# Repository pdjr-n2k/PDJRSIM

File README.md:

# PDJRSIM - NMEA 2000 switch input module

This project provides a
[hardware design](./hardware/)
and associated
[firmware](./firmware)
for a 16-channel NMEA 2000 switch input module.

There is also a
[User Manual](./docs)
for a device constructed from these components.

**PDJRSIM** is a specialisation of
[NOP100](https://github.com/preeve9534/NOP100).

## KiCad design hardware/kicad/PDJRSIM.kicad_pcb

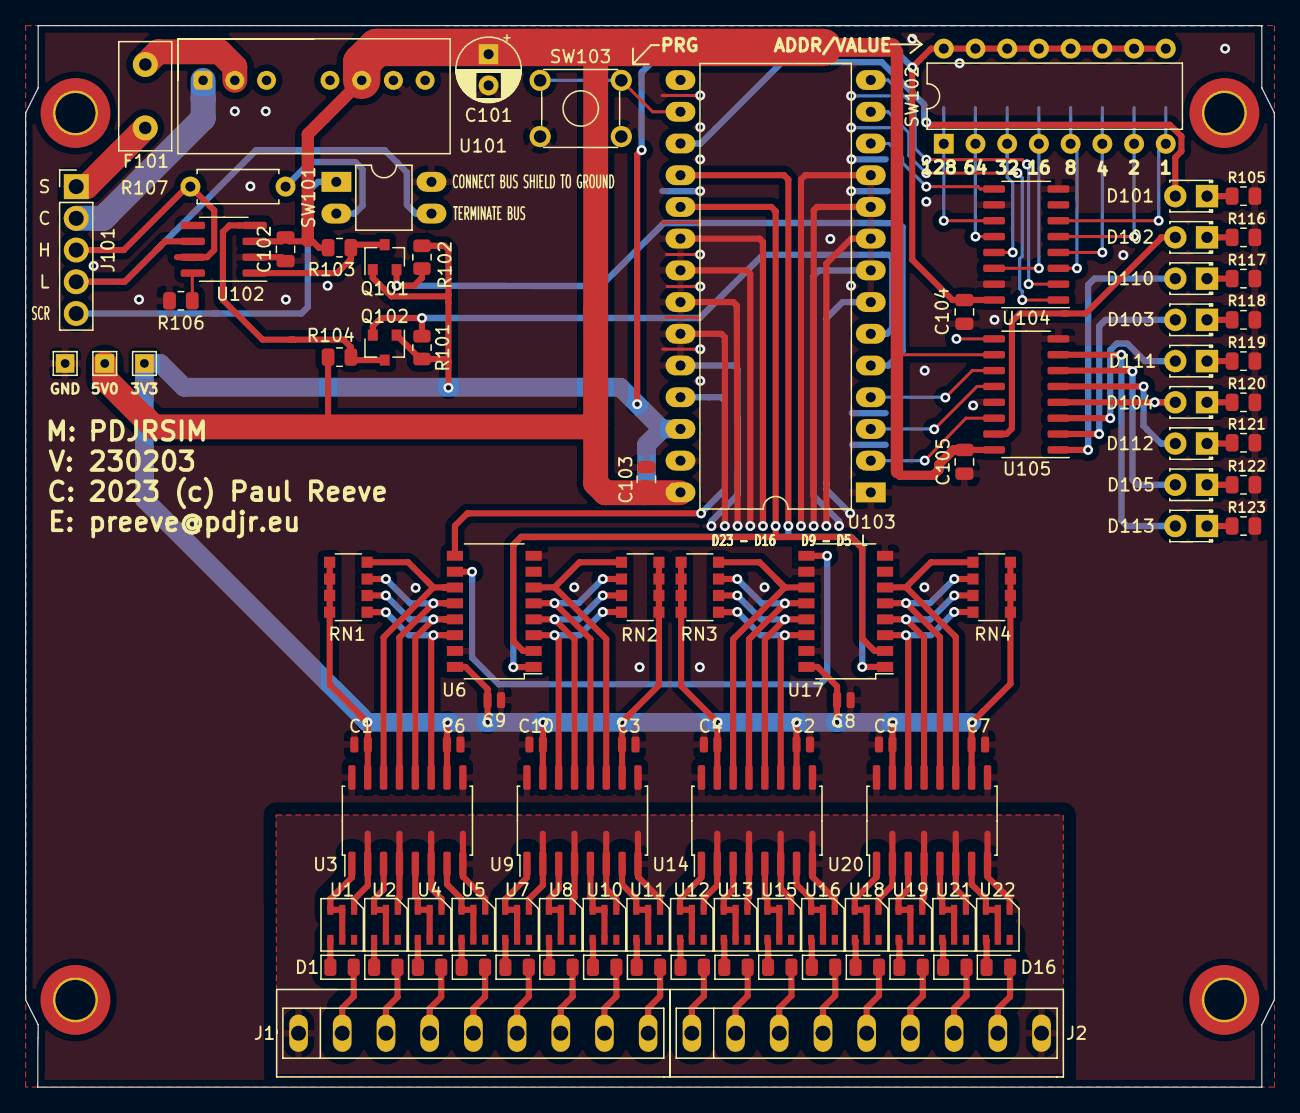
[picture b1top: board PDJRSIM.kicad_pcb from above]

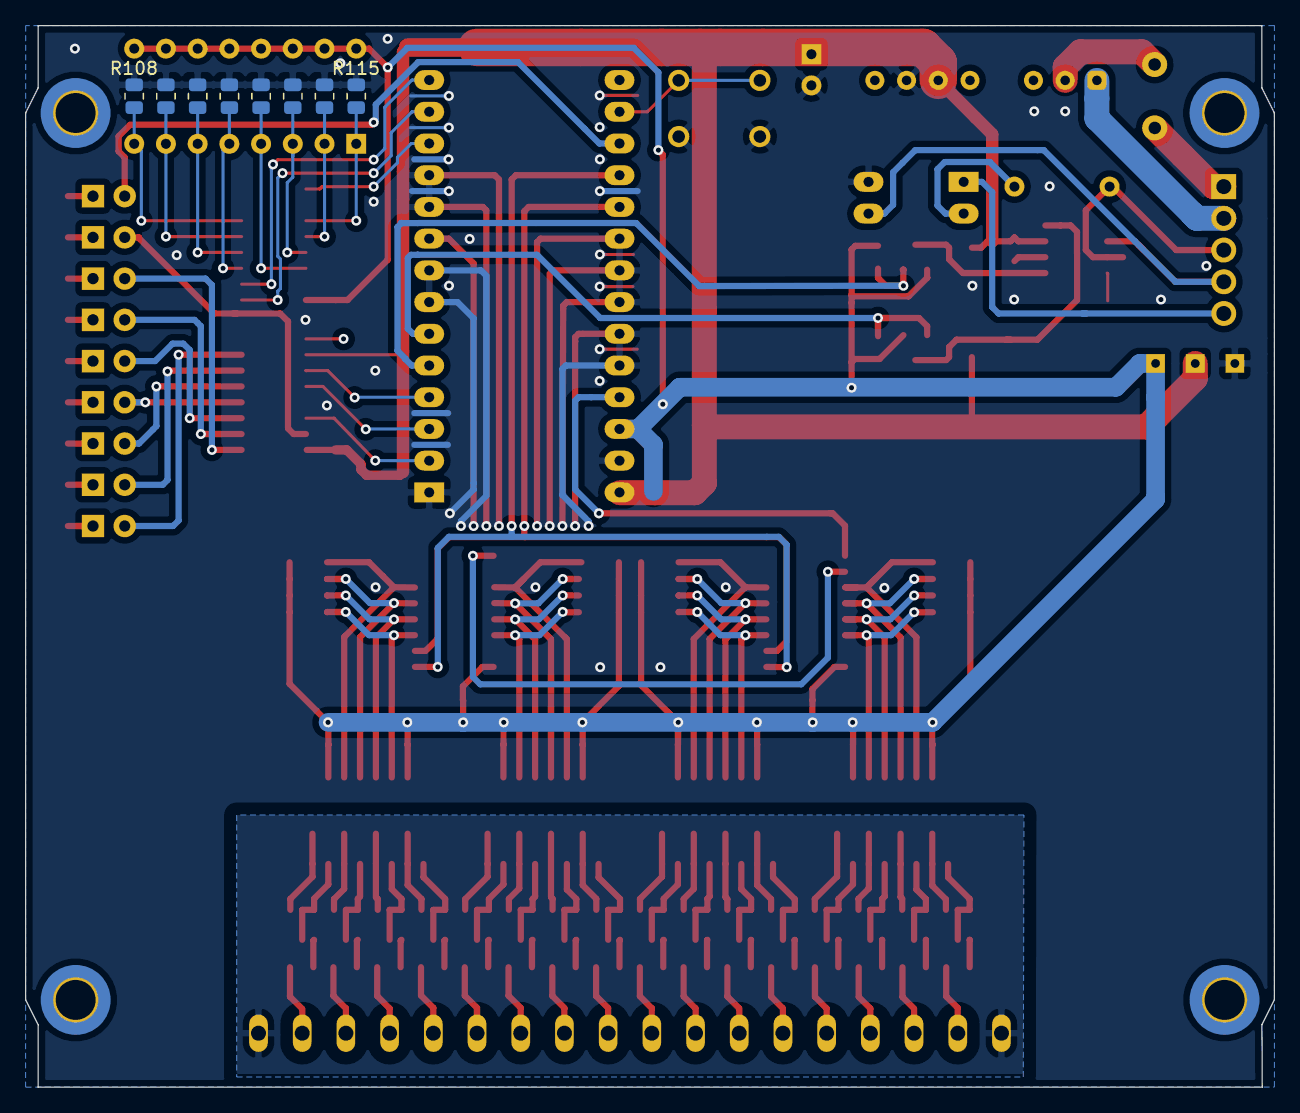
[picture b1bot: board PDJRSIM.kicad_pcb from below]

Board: 2 copper layers, 100.0 x 85.0 mm, 105 parts (8 on the bottom side), 117 nets.

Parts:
C1, C2, C3, C4, C5, C6, C7, C8, C9, C10: 100nF; C_0504_1310Metric
C101: 100nF; CP_Radial_D5.0mm_P2.50mm
C102, C103, C104, C105: 100nF; C_0805_2012Metric
D1, D2, D3, D4, D5, D6, D7, D8, D9, D10, D11, D12, D13, D14, D15, D16: D_Small; D_0805_2012Metric
D101, D102, D103, D104, D105, D110, D111, D112, D113: LED; LED_D1.8mm_W3.3mm_H2.4mm
F101: 1A; Fuse_Littelfuse_395Series
J1, J2: Screw_Terminal_01x09; 897-1357-9-PIN-3-5-CONN
J101: CAN; PinHeader_1x05_P2.54mm_Vertical
Q101, Q102: BSS138; SOT-23
R101, R102, R103, R104: 10K 0.125W; R_0805_2012Metric
R105, R116, R117, R118, R119, R120, R121, R122, R123: 560R; R_0805_2012Metric
R106, R108, R109, R110, R111, R112, R113, R114, R115: 4K7 0.125W; R_0805_2012Metric
R107: 120R 0.5W; R_Axial_DIN0207_L6.3mm_D2.5mm_P7.62mm_Horizontal
RN1, RN2, RN3, RN4: 4K; R_Array_Convex_4x1206
SW101: BUS; DIP-4_W7.62mm_LongPads
SW102: ADDR/VALUE; DIP-16_W7.62mm
SW103: PRG; SW_TH_Tactile_Omron_B3F-10xx
TEST 5V0, TEST 5V0#2: TestPoint_THTPad_1.5x1.5mm_Drill0.7mm
U1, U2, U4, U5, U7, U8, U10, U11, U12, U13, U15, U16, U18, U19, U21, U22: BCR401
U3, U9, U14, U20: ASCL-6400; SO-16_5.3x10.2mm_P1.27mm
U6, U17: 74LS165; SOP-16_4.4x10.4mm_P1.27mm
U101: TMR-2-2411; TMR_2411
U102: MCP2551-I-P; SOIC-8_3.9x4.9mm_P1.27mm
U103: Teensy_4.0; DIP-28_W15.24mm_LongPads
U104: 74HC165; SO-16_3.9x9.9mm_P1.27mm
U105: 74HCT595; SO-16_3.9x9.9mm_P1.27mm

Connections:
+3V3: C1.1, C2.1, C3.1, C4.1, C5.1, C6.1, C7.1, C8.1, C9.1, C10.1, C104.1, Q101.1, Q102.1, R101.2, R102.2, RN1.5, RN1.6, RN1.7, RN1.8, RN2.5, RN2.6, RN2.7, RN2.8, RN3.5, RN3.6, RN3.7, RN3.8, RN4.5, RN4.6, RN4.7, RN4.8, SW102.9, SW102.10, SW102.11, SW102.12, SW102.13, SW102.14, SW102.15, SW102.16, TEST 5V0.1, U3.10, U3.15, U6.16, U9.10, U9.15, U14.10, U14.15, U17.16, U20.10, U20.15, U103.26, U104.16
+5V: C101.1, C102.1, C103.1, C105.1, R103.2, R104.2, TEST 5V0#2.1, U101.6, U102.3, U103.28, U105.10, U105.16
/CAN_RX: Q102.2, R101.1, U103.6
/CAN_TX: Q101.2, R102.1, U103.5
/D16: U6.1, U17.1, U103.18
/D17: U6.2, U17.2, U103.19
/D23: U6.9, U103.25
/PISO_CP: U103.14, U104.2
/PISO_PL: U103.13, U104.1
/PISO_Q7: U103.12, U104.9
/PRG: SW103.1, SW103.2, U103.16
/SIPO_CLOCK: U103.4, U105.11
/SIPO_DATA: U103.2, U105.14
/SIPO_LATCH: U103.3, U105.12
GND: C1.2, C2.2, C3.2, C4.2, C5.2, C6.2, C7.2, C8.2, C9.2, C10.2, C101.2, C102.2, C103.2, C104.2, C105.2, R105.2, R106.1, R108.2, R109.2, R110.2, R111.2, R112.2, R113.2, R114.2, R115.2, R116.2, R117.2, R118.2, R119.2, R120.2, R121.2, R122.2, R123.2, SW101.4, SW103.3, SW103.4, U3.9, U3.16, U6.8, U6.15, U9.9, U9.16, U14.9, U14.16, U17.8, U17.10, U17.15, U20.9, U20.16, U101.7, U102.2, U103.1, U103.7, U103.8, U103.9, U103.10, U103.11, U103.20, U103.21, U103.22, U103.23, U103.24, U103.27, U104.8, U104.10, U104.15, U105.8, U105.13
unnamed: D1.1, U1.4
unnamed: D1.2, J1.2
unnamed: D2.1, U2.4
unnamed: D2.2, J1.3
unnamed: D3.1, U4.4
unnamed: D3.2, J1.4
unnamed: D4.1, U5.4
unnamed: D4.2, J1.5
unnamed: D5.1, U7.4
unnamed: D5.2, J1.6
unnamed: D6.1, U8.4
unnamed: D6.2, J1.7
unnamed: D7.1, U10.4
unnamed: D7.2, J1.8
unnamed: D8.1, U11.4
unnamed: D8.2, J1.9
unnamed: D9.1, U12.4
unnamed: D9.2, J2.1
unnamed: D10.1, U13.4
unnamed: D10.2, J2.2
unnamed: D11.1, U15.4
unnamed: D11.2, J2.3
unnamed: D12.1, U16.4
unnamed: D12.2, J2.4
unnamed: D13.1, U18.4
unnamed: D13.2, J2.5
unnamed: D14.1, U19.4
unnamed: D14.2, J2.6
unnamed: D15.1, U21.4
unnamed: D15.2, J2.7
unnamed: D16.1, U22.4
unnamed: D16.2, J2.8
unnamed: D101.1, R105.1
unnamed: D101.2, U103.17
unnamed: D102.1, R116.1
unnamed: D102.2, U105.15
unnamed: D103.1, R118.1
unnamed: D103.2, U105.2
unnamed: D104.1, R120.1
unnamed: D104.2, U105.4
unnamed: D105.1, R122.1
unnamed: D105.2, U105.6
unnamed: D110.1, R117.1
unnamed: D110.2, U105.1
unnamed: D111.1, R119.1
unnamed: D111.2, U105.3
unnamed: D112.1, R121.1
unnamed: D112.2, U105.5
unnamed: D113.1, R123.1
unnamed: D113.2, U105.7
unnamed: F101.1, J101.1
unnamed: F101.2, U101.2
unnamed: J1.1, J2.9, U1.1, U2.1, U3.2, U3.4, U3.6, U3.8, U4.1, U5.1, U7.1, U8.1, U9.2, U9.4, U9.6, U9.8, U10.1, U11.1, U12.1, U13.1, U14.2, U14.4, U14.6, U14.8, U15.1, U16.1, U18.1, U19.1, U20.2, U20.4, U20.6, U20.8, U21.1, U22.1
unnamed: J101.2, U101.1
unnamed: J101.3, R107.1, U102.7
unnamed: J101.4, SW101.3, U102.6
unnamed: J101.5, SW101.1
unnamed: Q101.3, R103.1, U102.1
unnamed: Q102.3, R104.1, U102.4
unnamed: R106.2, U102.8
unnamed: R107.2, SW101.2
unnamed: R108.1, SW102.8, U104.6
unnamed: R109.1, SW102.7, U104.5
unnamed: R110.1, SW102.6, U104.4
unnamed: R111.1, SW102.5, U104.3
unnamed: R112.1, SW102.4, U104.14
unnamed: R113.1, SW102.3, U104.13
unnamed: R114.1, SW102.2, U104.12
unnamed: R115.1, SW102.1, U104.11
unnamed: RN1.1, U3.11, U6.14
unnamed: RN1.2, U3.12, U6.13
unnamed: RN1.3, U3.13, U6.12
unnamed: RN1.4, U3.14, U6.11
unnamed: RN2.1, U6.6, U9.11
unnamed: RN2.2, U6.5, U9.12
unnamed: RN2.3, U6.4, U9.13
unnamed: RN2.4, U6.3, U9.14
unnamed: RN3.1, U14.11, U17.14
unnamed: RN3.2, U14.12, U17.13
unnamed: RN3.3, U14.13, U17.12
unnamed: RN3.4, U14.14, U17.11
unnamed: RN4.1, U17.6, U20.11
unnamed: RN4.2, U17.5, U20.12
unnamed: RN4.3, U17.4, U20.13
unnamed: RN4.4, U17.3, U20.14
unnamed: U1.2, U1.3, U1.5, U3.1
unnamed: U2.2, U2.3, U2.5, U3.3
unnamed: U3.5, U4.2, U4.3, U4.5
unnamed: U3.7, U5.2, U5.3, U5.5
unnamed: U7.2, U7.3, U7.5, U9.1
unnamed: U8.2, U8.3, U8.5, U9.3
unnamed: U9.5, U10.2, U10.3, U10.5
unnamed: U9.7, U11.2, U11.3, U11.5
unnamed: U12.2, U12.3, U12.5, U14.1
unnamed: U13.2, U13.3, U13.5, U14.3
unnamed: U14.5, U15.2, U15.3, U15.5
unnamed: U14.7, U16.2, U16.3, U16.5
unnamed: U6.10, U17.9
unnamed: U18.2, U18.3, U18.5, U20.1
unnamed: U19.2, U19.3, U19.5, U20.3
unnamed: U20.5, U21.2, U21.3, U21.5
unnamed: U20.7, U22.2, U22.3, U22.5

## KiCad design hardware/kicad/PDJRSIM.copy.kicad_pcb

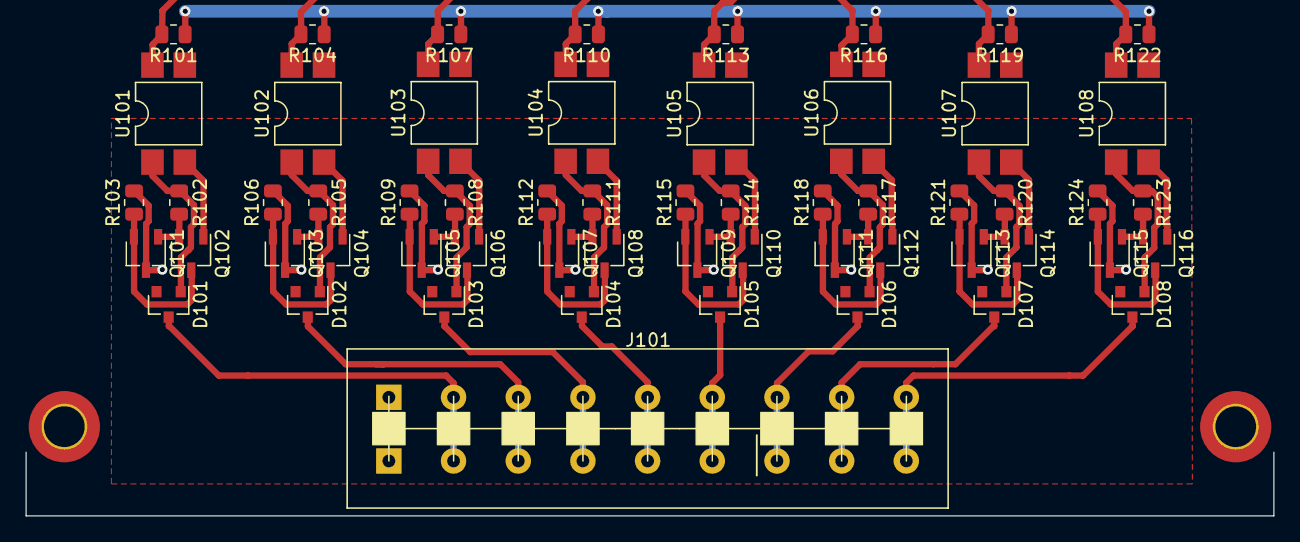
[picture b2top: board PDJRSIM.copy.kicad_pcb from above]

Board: 2 copper layers, 57 parts (0 on the bottom side), 51 nets.

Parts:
D101, D102, D103, D104, D105, D106, D107, D108: IN4007; D_SOT-23_ANK
J101: Screw_Terminal_01x09; CAMDEN_BOSS_CSTBV2-9_TERMINAL
Q101, Q103, Q105, Q107, Q109, Q111, Q113, Q115: BC547; TSOT-23
Q102, Q104, Q106, Q108, Q110, Q112, Q114, Q116: BC337-40; TSOT-23
R101, R104, R107, R110, R113, R116, R119, R122: 4K7 0.125W; R_0805_2012Metric
R102, R105, R108, R111, R114, R117, R120, R123: 10K 0.5W; R_0805_2012Metric
R103, R106, R109, R112, R115, R118, R121, R124: 100R 0.25W; R_0805_2012Metric
U101, U102, U103, U104, U105, U106, U107, U108: SFH617A-1; SMDIP-4_W7.62mm

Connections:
+3V3: R101.1, R104.1, R107.1, R110.1, R113.1, R116.1, R119.1, R122.1
/D16: R122.2, U108.4
/D17: R119.2, U107.4
/D18: R116.2, U106.4
/D19: R113.2, U105.4
/D20: R110.2, U104.4
/D21: R107.2, U103.4
/D22: R104.2, U102.4
/D23: R101.2, U101.4
/SPST_GND: J101.1, Q101.3, Q103.3, Q105.3, Q107.3, Q109.3, Q111.3, Q113.3, Q115.3, R103.2, R106.2, R109.2, R112.2, R115.2, R118.2, R121.2, R124.2
GND: U101.3, U102.3, U103.3, U104.3, U105.3, U106.3, U107.3, U108.3
unnamed: D101.1, J101.2
unnamed: D101.2, R102.1, U101.1
unnamed: D102.1, J101.3
unnamed: D102.2, R105.1, U102.1
unnamed: D103.1, J101.4
unnamed: D103.2, R108.1, U103.1
unnamed: D104.1, J101.5
unnamed: D104.2, R111.1, U104.1
unnamed: D105.1, J101.6
unnamed: D105.2, R114.1, U105.1
unnamed: D106.1, J101.7
unnamed: D106.2, R117.1, U106.1
unnamed: D107.1, J101.8
unnamed: D107.2, R120.1, U107.1
unnamed: D108.1, J101.9
unnamed: D108.2, R123.1, U108.1
unnamed: Q101.1, Q102.2, R102.2
unnamed: Q101.2, Q102.3, R103.1
unnamed: Q102.1, U101.2
unnamed: Q103.1, Q104.2, R105.2
unnamed: Q103.2, Q104.3, R106.1
unnamed: Q104.1, U102.2
unnamed: Q105.1, Q106.2, R108.2
unnamed: Q105.2, Q106.3, R109.1
unnamed: Q106.1, U103.2
unnamed: Q107.1, Q108.2, R111.2
unnamed: Q107.2, Q108.3, R112.1
unnamed: Q108.1, U104.2
unnamed: Q109.1, Q110.2, R114.2
unnamed: Q109.2, Q110.3, R115.1
unnamed: Q110.1, U105.2
unnamed: Q111.1, Q112.2, R117.2
unnamed: Q111.2, Q112.3, R118.1
unnamed: Q112.1, U106.2
unnamed: Q113.1, Q114.2, R120.2
unnamed: Q113.2, Q114.3, R121.1
unnamed: Q114.1, U107.2
unnamed: Q115.1, Q116.2, R123.2
unnamed: Q115.2, Q116.3, R124.1
unnamed: Q116.1, U108.2

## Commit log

2022-07-14 First initialisation
    Raw copy of TMP108
2022-08-01 First circuit design
2022-08-03 Revised opto isolation
2022-08-05 Constant current inputs
2022-08-08 Draft user guide
2022-08-17 Beginning to code...
2022-08-20 First successful compile
2022-08-22 README update
2022-08-25 Tidy up
2022-08-26 Trivial updates
2022-08-26 Tweaks
2022-09-30 New board size
2022-10-01 PCB tweaks
2022-10-01 PCB tweak
2022-10-09 Stuff
2022-10-09 Debounce
2022-10-10 Layout
2022-10-10 PCB layout
2022-10-10 Update PCB
2022-10-13 Add transmit LED
2022-10-13 Transmit LED
2022-10-14 Tweak
2022-10-14 Change PCB conn
2022-10-14 Update connector
2022-10-15 Update PCB hole sizes
2022-10-15 Centre switch connector
2022-10-15 Terak
2022-10-15 Add mount holes
2022-10-15 Change to Camden Boss connector
2022-10-25 PCB reroute
2022-10-28 Refactor
2022-10-29 Change relay terminal
2022-11-05 Silk text
2022-11-05 Add silk text
2022-11-07 Pcb resize
2022-11-29 Add jumper alternative to SW2
2022-11-30 Swap passive SMD for TH
2022-11-30 PCB silk update
2022-12-01 Revise for 3.3V
2022-12-01 Migrate to Teens 4.0
    3.3V inputs
2022-12-03 Move to SMD
2022-12-04 SIlk edit
2022-12-04 Switch to software debounce
2022-12-04 Refill
2022-12-05 Add test points
2022-12-05 Test points
2022-12-06 Revise PCB
2022-12-06 Edit silk.
2022-12-06 Silk edit.
2022-12-19 Rework
2022-12-19 Documentation
2022-12-19 Relay PCB
2022-12-25 Parameter tweak.
2022-12-26 Refactor.
2022-12-27 Use new NOP100
2023-01-13 New model
2023-01-14 Tidy up.
2023-01-16 Get rid of MacOS artifacts
2023-01-20 Use default constructor
2023-02-01 New PCB layout
2023-02-05 Gerber order
2023-02-06 Shift to SIPO interface
2023-02-07 Rename
2023-02-07 Fix a break
